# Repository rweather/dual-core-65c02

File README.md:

Dual Core 65C02 Computer
========================

This repository contains schematics, documentation, and program code for my
dual core 65C02 computer.  The computer has two 65C02 microprocessors,
sharing a common memory and I/O bus for symmetric multiprocessing (SMP),
8-bit style.

Here is what it looks like on a PCB.  The two large 40-pin chips at the
top are the CPU's.

If you would like to build your own, I have
[shared the design on PCBway](https://www.pcbway.com/project/shareproject/Dual_Core_65C02_Computer_47504aca.html).  Or contact me at the e-mail address
below and I might still have some spare PCB's I can mail out.

## How did this happen?

Steve Wozniak's design of the Apple II avoided video snow by alternating
access to main memory between the 6502 CPU and the video system.  The two
systems cannot collide and thus cannot create snow.

I asked myself, "Could I do that with two CPU's?" and an obsession was born.

## How does it work?

The W65C02S CPU from Western Digital simplifies things.  The BE
(bus enable) pin can be pulled low to take the CPU completely off the bus
temporarily.  By alternating the bus enables, each CPU can be given
access to memory and I/O in turn.

It would theoretically be possible to do this with the original 6502
microprocessor, but extra bus transceivers would be required as
the original 6502 does not have a BE pin.  The Apple II design
includes bus transceivers for exactly this purpose.

The main 12MHz crystal oscillator is divided down into a number of
component clock signals:

<table border="1">
<tr><td><b>Signal</b></td><td><b>Description</b></td></tr>
<tr><td>CPU1 CLK</td><td>2MHz clock for CPU1</td></tr>
<tr><td>CPU2 CLK</td><td>2MHz clock for CPU2</td></tr>
<tr><td>CPU1 BUSEN</td><td>2MHz bus enable for CPU1</td></tr>
<tr><td>CPU2 BUSEN</td><td>2MHz bus enable for CPU2</td></tr>
<tr><td>COMMON CLK</td><td>4MHz common clock for memory and I/O</td></tr>
</table>

## Memory map

<table border="1">
<tr><td><b>Address Range</b></td><td><b>Description</b></td></tr>
<tr><td>$0000 - $00FF</td><td>Zero page for CPU 1</td></tr>
<tr><td>$0100 - $01FF</td><td>Stack for CPU 1</td></tr>
<tr><td>$0200 - $02FF</td><td>Zero page for CPU 2</td></tr>
<tr><td>$0300 - $03FF</td><td>Stack for CPU 2</td></tr>
<tr><td>$0400 - $7FFF</td><td>Shared RAM (31K)</td></tr>
<tr><td>$8000 - $81FF</td><td>Main board I/O</td></tr>
<tr><td>$8200 - $83FF</td><td>Versatile Interface Adapter (VIA)</td></tr>
<tr><td>$8400 - $84FF</td><td>Asynchronous Communications Interface Adapter (ACIA)</td></tr>
<tr><td>$8600 - $87FF</td><td>RCbus I/O address space</td></tr>
<tr><td>$8800 - $8FFF</td><td>Spare I/O address space</td></tr>
<tr><td>$9000 - $BFFF</td><td>Unused memory space (12K)</td></tr>
<tr><td>$C000 - $FFFF</td><td>CPU-specific ROM (16K)</td></tr>
</table>

Address ranges $0000 - $01FF and $0200 - $03FF are swapped in CPU2 so that
CPU2 sees its zero page and stack starting at $0000 and sees CPU1's
zero page and stack starting at $0200.  This keeps the zero pages and
stacks separate.

The design uses a 32K EEPROM, divided into two 16K halves.  CPU1 sees
the first half of the ROM and CPU2 sees the second half of the ROM.
Thus, different programs can run on each CPU, or the same program.
It is up to the programmer.  This repository contains a minimal
[BIOS](src/common/bios.s) for initializing and accessing the hardware.

The main board decodes 8 I/O device address ranges between $8000 and $8FFF,
each consisting of 512 bytes ($0200 hex).  Four of these are used for
purposes on the main board.  The others are spare for expansion boards.

The 12K of unused memory space can be used for bank-switched RAM, video
memory, cartridge ROM's, or anything you want.

## Mutual exclusion

In any multi-core system, some method is required to synchronise access to
memory and I/O across the cores.  The 65C02 takes multiple clock cycles to
perform a read-modify-write instruction like "INC" or "DEC".  The other core
could get in the middle of that and mess things up.

According to the W65C02S datasheet, the ML pin can be used to co-ordinate
bus accesses when read-modify-write instructions are being performed.
I experimented with a method to "stretch" the bus enable signals to
delay the other CPU while the current one was performing a read-modify-write.
But I wasn't able to make it stable.

Instead, I use two flip-flops and some I/O pins to provide mutual exclusion.
In Logisim, it looks like this:

When CPU1 wants the mutex, it raises the Want1 pin (address $8107, bit 0) and
then polls the Acquired1 signal (address $8080, bit 7).  Once the acquired
signal goes high, CPU1 has the mutex.  To release the mutex, lower the
Want1 pin.

CPU2 does the same thing with Want2 (address $8106, bit 0) and
Acquired2 (address $8080, bit 6).

The mutex is "fair" in the sense that when one CPU lowers its Want pin,
the other CPU is guaranteed to immediately get the mutex if it had
previously raised its Want pin.  It is impossible for one CPU to
hog the mutex, except by forgetting to unlock it.

The [BIOS](src/common/bios.s) provides the subroutines `mutex_lock`,
`mutex_unlock`, and `mutex_try_lock` to make things easier for the
programmer.  The implementation is different for each CPU.

## System millisecond tick timer

There is a 555 timer in the circuit that delivers a 1000Hz signal to the
NMI pins on each of the CPU's.  A potentiometer allows the frequency to
be dialed in precisely.

The default NMI handler in the BIOS increments a 24-bit millisecond
tick counter which wraps around after 4 hours and 39 minutes.
Call the `systick` subroutine to fetch the value of the tick counter
safely into the Y:X:A register triple.

NMI can interfere with foreground code and regular IRQ handlers,
which may affect timing-critical code.  There are jumpers in the circuit
that allow the 555 to be disconnected from one or both of the CPU's.

## Schematic and other technical information

* [PDF of the schematic](schematics/DualCore6502Whole/PDF/DualCore6502Whole.pdf)
* [Gerbers for the PCB](schematics/DualCore6502Whole/Gerber)
* [Parts list](doc/parts-list.md)

## What can't it do?

DMA is not currently supported.  Pausing the clocks and bus enables to allow
external access to the bus is complicated.  Too complicated for my feeble brain.
Maybe in the next version.

In theory the W65C02S can go up to 14MHz.  While SRAM that is faster than
70ns access time is possible, AT28C256 EEPROM chips form are typically 150ns.
In practice, this limits the maximum memory speed to about 4MHz.
AT27C256 EEPROM's can go down to 45ns but they are not pin-compatible and
that still only gets us to 8MHz or so.  An alternative memory design with
wait states may allow pushing the performance further.  Once again,
my feeble brain isn't up to the task.

Could we have more CPU's?  Four?  Eight?  In theory, yes.  But memory
access times limit things.  The speed of the individual CPU's would need to be
reduced to 1MHz to allow four on the bus, executing one after another.
The effective speed of the system would remain at 4MHz.  An alternate design
might give each CPU its own fast SRAM, with wait states for access to
common RAM, ROM, and I/O.

## TODO

* Machine monitor for loading programs into RAM via the serial port and
debugging them (partially done).
* Devise a multi-core operating system to showcase the capabilities.

## License

Distributed under the terms of the MIT license.

## Contact

For more information on this code, to report bugs, or to suggest
improvements, please contact the author Rhys Weatherley via
[email](mailto:rhys.weatherley@gmail.com).

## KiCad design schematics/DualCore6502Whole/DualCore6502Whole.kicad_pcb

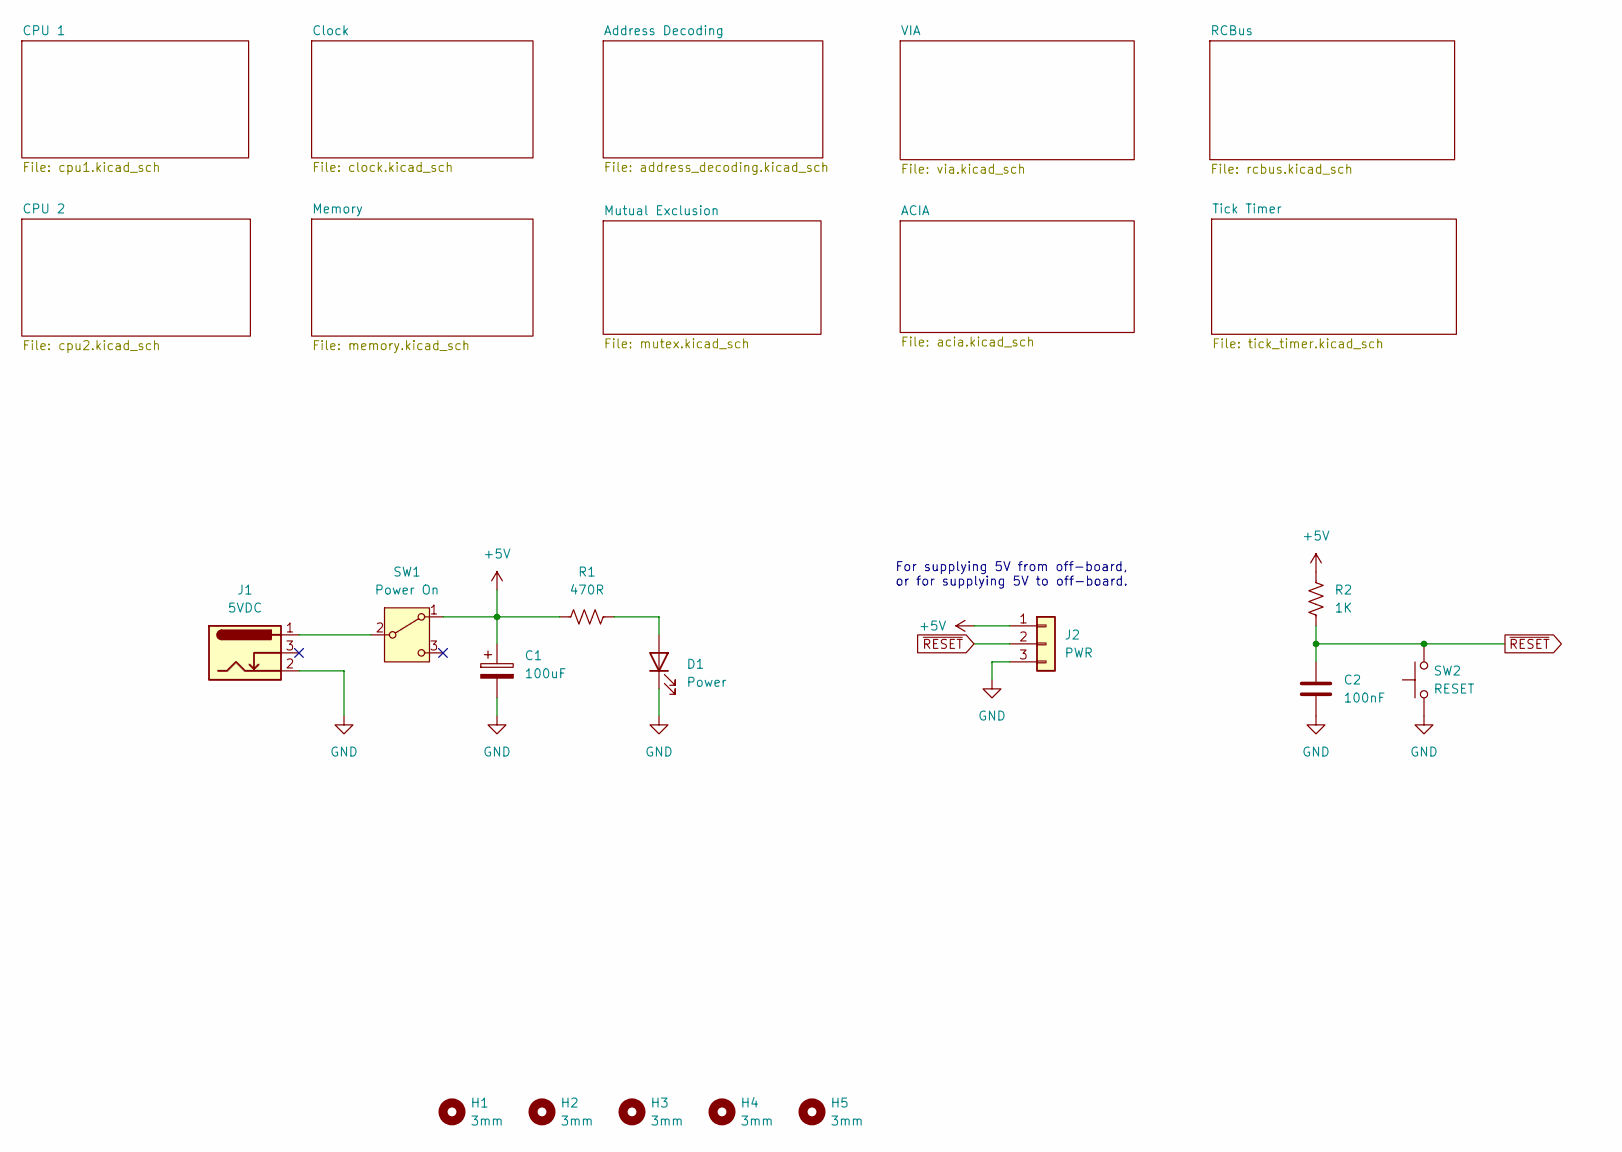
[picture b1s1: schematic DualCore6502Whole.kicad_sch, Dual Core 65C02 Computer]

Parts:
C1: 100uF; CP_Radial_D6.3mm_P2.50mm
C2: 100nF; C_Disc_D5.0mm_W2.5mm_P5.00mm
D1: Power; LED_D5.0mm
H1, H2, H3, H4, H5: 3mm; MountingHole_3mm
J1: 5VDC; BarrelJack_Horizontal
J2: PWR; PhoenixContact_MC_1,5_3-G-5.08_1x03_P5.08mm_Horizontal
R1: 470R; R_Axial_DIN0207_L6.3mm_D2.5mm_P10.16mm_Horizontal
R2: 1K; R_Axial_DIN0207_L6.3mm_D2.5mm_P10.16mm_Horizontal
SW1: Power On; PinHeader_1x03_P2.54mm_Vertical
SW2: RESET; SW_PUSH_6mm_H5mm

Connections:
+5V: C1.1, J2.1, R1.1, R2.1, SW1.1 (A); also elsewhere on the board
GND: C1.2, C2.2, D1.1 (K), J1.2, J2.3, SW2.1; also elsewhere on the board
unnamed: D1.2 (A), R1.2
unnamed: J1.1, SW1.2 (B)
~RESET: C2.1, J2.2, R2.2, SW2.2; also elsewhere on the board

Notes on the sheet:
For supplying 5V from off-board, or for supplying 5V to off-board.

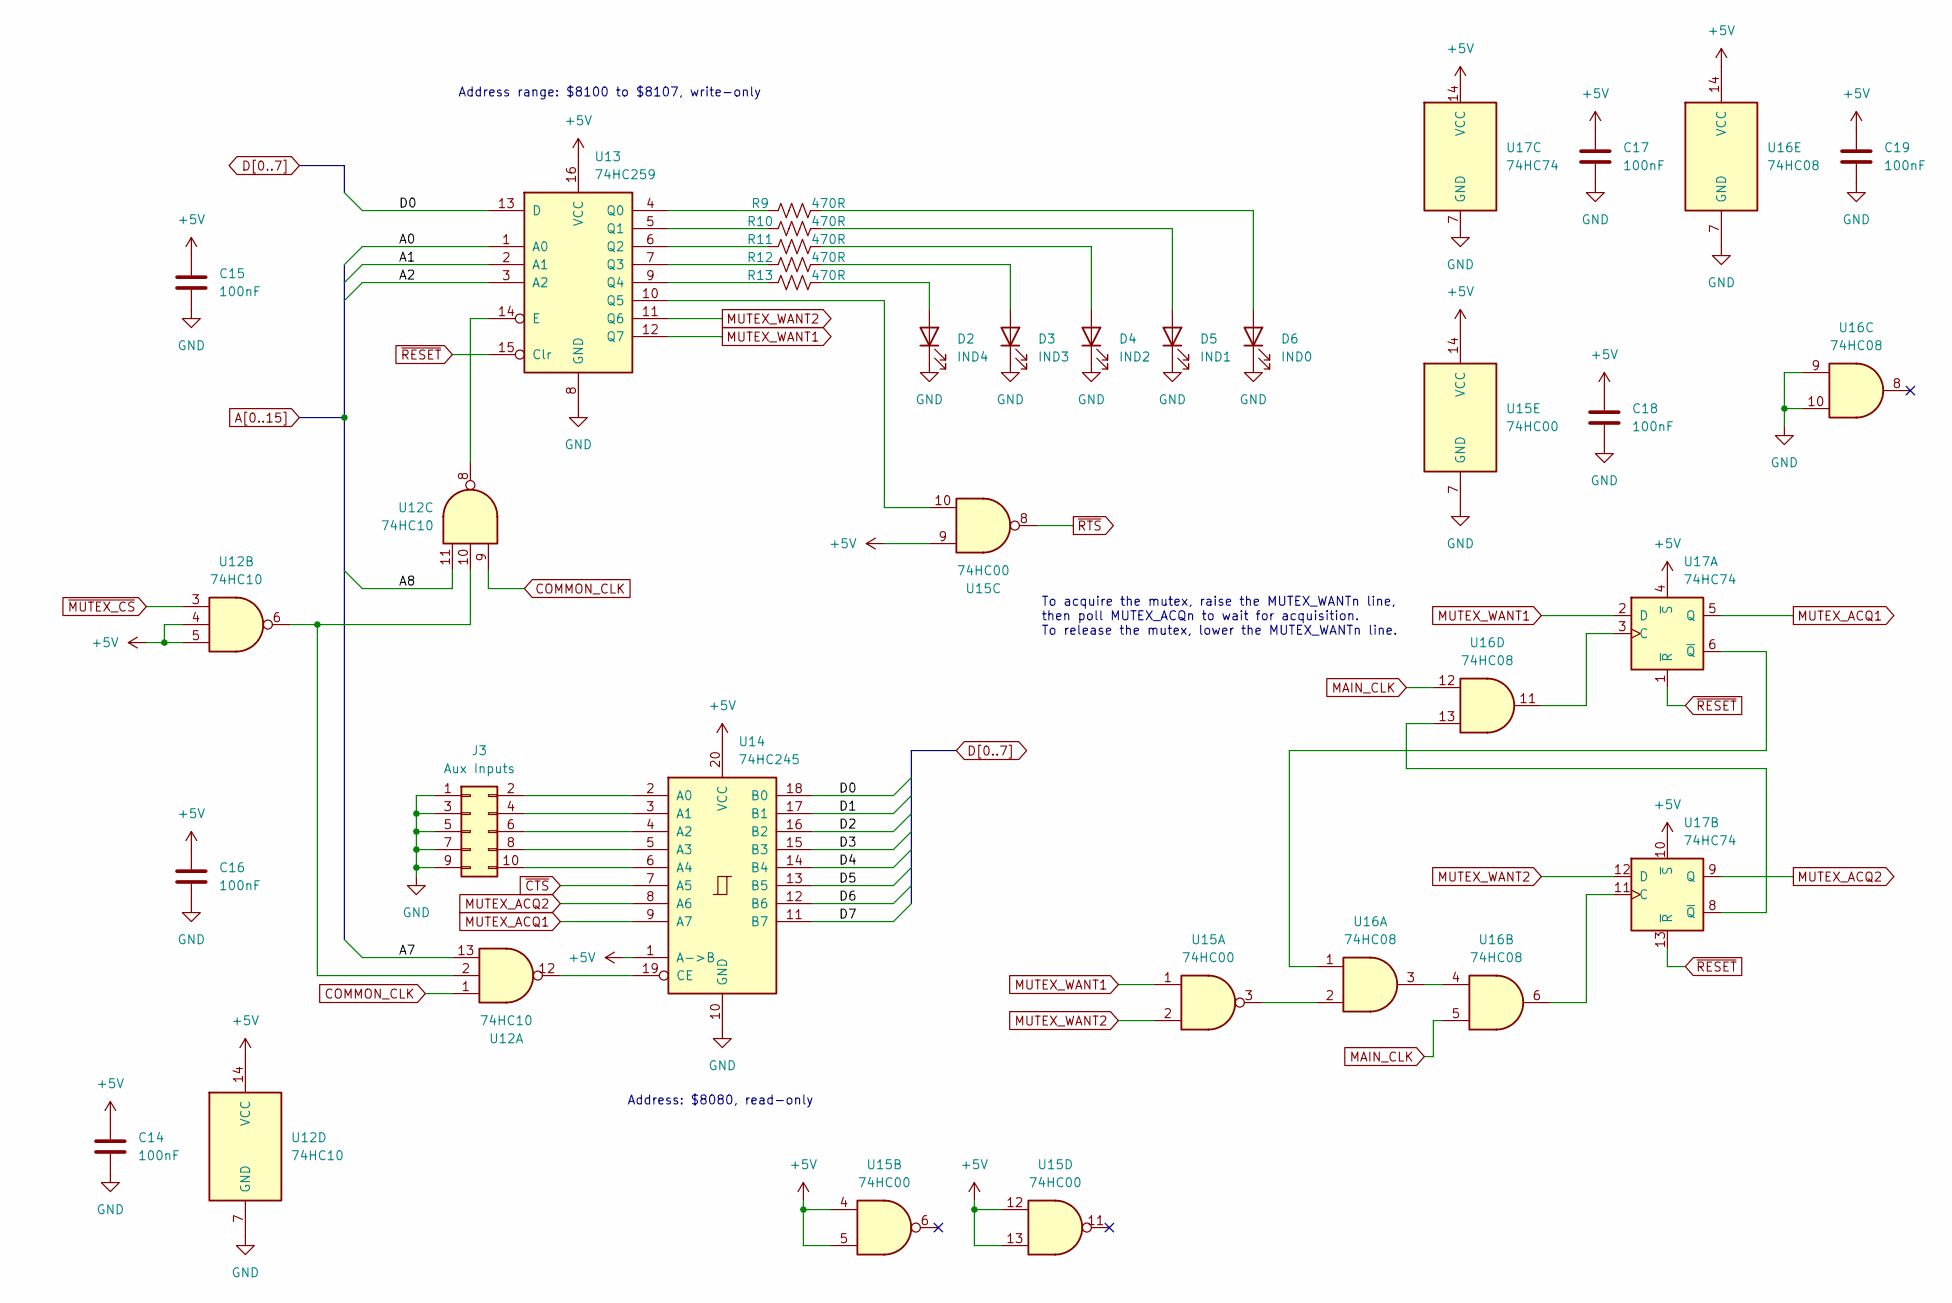
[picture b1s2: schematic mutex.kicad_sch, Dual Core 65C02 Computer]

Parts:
C14, C15, C16, C17, C18, C19: 100nF; C_Disc_D5.0mm_W2.5mm_P5.00mm
D2: IND4; LED_D3.0mm
D3: IND3; LED_D3.0mm
D4: IND2; LED_D3.0mm
D5: IND1; LED_D3.0mm
D6: IND0; LED_D3.0mm
J3: Aux Inputs; PinHeader_2x05_P2.54mm_Vertical
R9, R10, R11, R12, R13: 470R; R_Axial_DIN0207_L6.3mm_D2.5mm_P10.16mm_Horizontal
U12: 74HC10; DIP-14_W7.62mm_Socket
U13: 74HC259; DIP-16_W7.62mm_Socket
U14: 74HC245; DIP-20_W7.62mm_Socket
U15: 74HC00; DIP-14_W7.62mm_Socket
U16: 74HC08; DIP-14_W7.62mm_Socket
U17: 74HC74; DIP-14_W7.62mm_Socket

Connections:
+5V: C14.1, C15.1, C16.1, C17.1, C18.1, C19.1, U12.4, U12.5, U12.14 (VCC), U13.16 (VCC), U14.1 (A->B), U14.20 (VCC), U15.4, U15.5, U15.9, U15.12, U15.13, U15.14 (VCC), U16.14 (VCC), U17.4 (~S), U17.10 (~S), U17.14 (VCC); also elsewhere on the board
A0: U13.1 (A0); also elsewhere on the board
A1: U13.2 (A1); also elsewhere on the board
A2: U13.3 (A2); also elsewhere on the board
A7: U12.13; also elsewhere on the board
A8: U12.11; also elsewhere on the board
COMMON_CLK: U12.1, U12.9; also elsewhere on the board
D0: U13.13 (D), U14.18 (B0); also elsewhere on the board
D1: U14.17 (B1); also elsewhere on the board
D2: U14.16 (B2); also elsewhere on the board
D3: U14.15 (B3); also elsewhere on the board
D4: U14.14 (B4); also elsewhere on the board
D5: U14.13 (B5); also elsewhere on the board
D6: U14.12 (B6); also elsewhere on the board
D7: U14.11 (B7); also elsewhere on the board
GND: C14.2, C15.2, C16.2, C17.2, C18.2, C19.2, D2.1 (K), D3.1 (K), D4.1 (K), D5.1 (K), D6.1 (K), J3.1, J3.3, J3.5, J3.7, J3.9, U12.7 (GND), U13.8 (GND), U14.10 (GND), U15.7 (GND), U16.7 (GND), U16.9, U16.10, U17.7 (GND); also elsewhere on the board
MAIN_CLK: U16.5, U16.12; also elsewhere on the board
MUTEX_ACQ1: U14.9 (A7), U17.5 (Q)
MUTEX_ACQ2: U14.8 (A6), U17.9 (Q)
MUTEX_WANT1: U13.12 (Q7), U15.1, U17.2 (D)
MUTEX_WANT2: U13.11 (Q6), U15.2, U17.12 (D)
unnamed: D2.2 (A), R13.2
unnamed: D3.2 (A), R12.2
unnamed: D4.2 (A), R11.2
unnamed: D5.2 (A), R10.2
unnamed: D6.2 (A), R9.2
unnamed: J3.2, U14.2 (A0)
unnamed: J3.4, U14.3 (A1)
unnamed: J3.6, U14.4 (A2)
unnamed: J3.8, U14.5 (A3)
unnamed: J3.10, U14.6 (A4)
unnamed: U12.2, U12.6, U12.10
unnamed: U12.8, U13.14 (E)
unnamed: R9.1, U13.4 (Q0)
unnamed: R10.1, U13.5 (Q1)
unnamed: R11.1, U13.6 (Q2)
unnamed: R12.1, U13.7 (Q3)
unnamed: R13.1, U13.9 (Q4)
unnamed: U13.10 (Q5), U15.10
unnamed: U12.12, U14.19 (CE)
unnamed: U15.3, U16.2
unnamed: U16.3, U16.4
unnamed: U16.11, U17.3 (C)
unnamed: U16.1, U17.6 (~Q)
unnamed: U16.6, U17.11 (C)
unnamed: U16.13, U17.8 (~Q)
~CTS: U14.7 (A5); also elsewhere on the board
~MUTEX_CS: U12.3; also elsewhere on the board
~RESET: U13.15 (Clr), U17.1 (~R), U17.13 (~R); also elsewhere on the board
~RTS: U15.8; also elsewhere on the board

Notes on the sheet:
Address range: $8100 to $8107, write-only
Address: $8080, read-only
To acquire the mutex, raise the MUTEX_WANTn line, then poll MUTEX_ACQn to wait for acquisition. To release the mutex, lower the MUTEX_WANTn line.

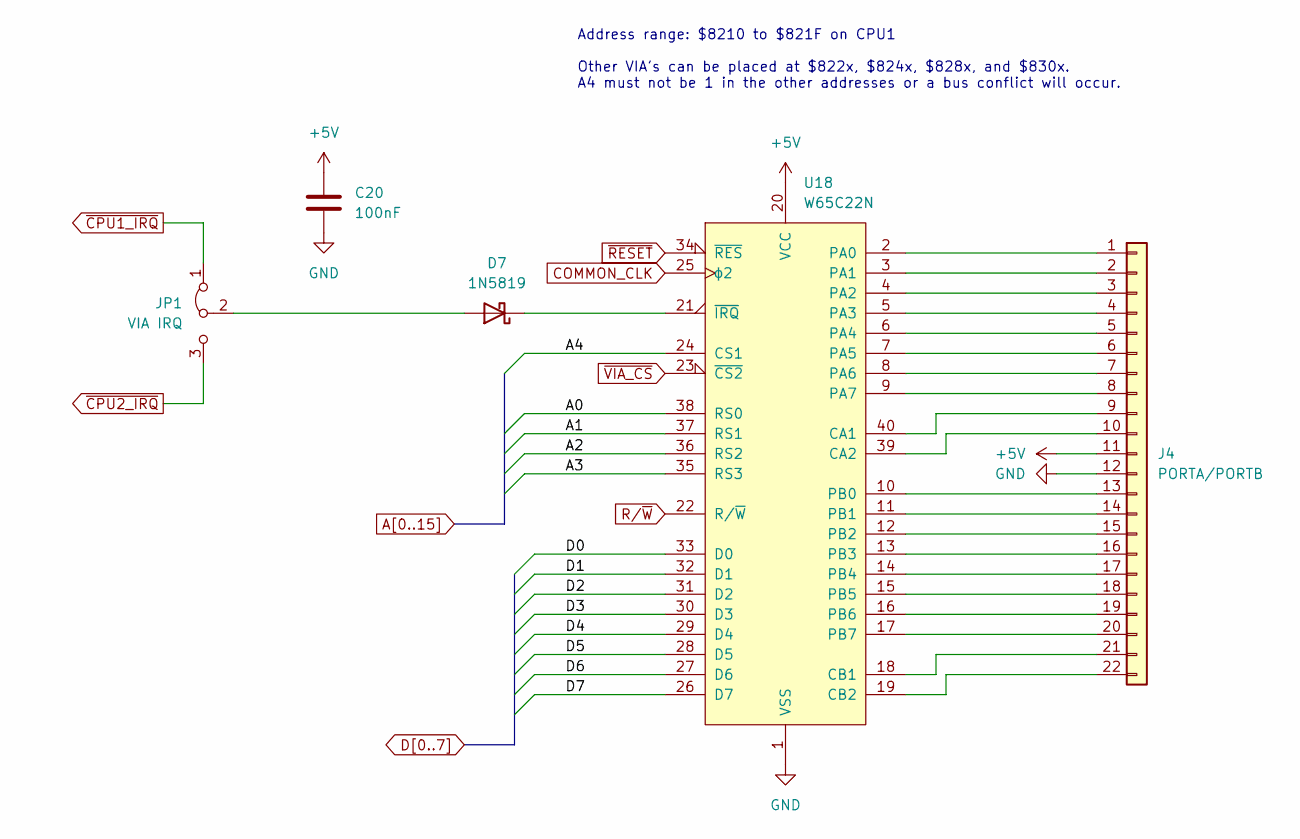
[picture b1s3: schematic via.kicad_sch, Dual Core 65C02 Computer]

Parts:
C20: 100nF; C_Disc_D5.0mm_W2.5mm_P5.00mm
D7: 1N5819; D_DO-41_SOD81_P10.16mm_Horizontal
J4: PORTA/PORTB; PinSocket_1x22_P2.54mm_Vertical
JP1: VIA IRQ; PinHeader_1x03_P2.54mm_Vertical
U18: W65C22N; DIP-40_W15.24mm_Socket

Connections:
+5V: C20.1, J4.11, U18.20 (VCC); also elsewhere on the board
A0: U18.38 (RS0); also elsewhere on the board
A1: U18.37 (RS1); also elsewhere on the board
A2: U18.36 (RS2); also elsewhere on the board
A3: U18.35 (RS3); also elsewhere on the board
A4: U18.24 (CS1); also elsewhere on the board
COMMON_CLK: U18.25 (ϕ2); also elsewhere on the board
D0: U18.33 (D0); also elsewhere on the board
D1: U18.32 (D1); also elsewhere on the board
D2: U18.31 (D2); also elsewhere on the board
D3: U18.30 (D3); also elsewhere on the board
D4: U18.29 (D4); also elsewhere on the board
D5: U18.28 (D5); also elsewhere on the board
D6: U18.27 (D6); also elsewhere on the board
D7: U18.26 (D7); also elsewhere on the board
GND: C20.2, J4.12, U18.1 (VSS); also elsewhere on the board
unnamed: D7.2 (A), JP1.2 (C)
unnamed: D7.1 (K), U18.21 (~IRQ)
unnamed: J4.1, U18.2 (PA0)
unnamed: J4.2, U18.3 (PA1)
unnamed: J4.3, U18.4 (PA2)
unnamed: J4.4, U18.5 (PA3)
unnamed: J4.5, U18.6 (PA4)
unnamed: J4.6, U18.7 (PA5)
unnamed: J4.7, U18.8 (PA6)
unnamed: J4.8, U18.9 (PA7)
unnamed: J4.9, U18.40 (CA1)
unnamed: J4.10, U18.39 (CA2)
unnamed: J4.13, U18.10 (PB0)
unnamed: J4.14, U18.11 (PB1)
unnamed: J4.15, U18.12 (PB2)
unnamed: J4.16, U18.13 (PB3)
unnamed: J4.17, U18.14 (PB4)
unnamed: J4.18, U18.15 (PB5)
unnamed: J4.19, U18.16 (PB6)
unnamed: J4.20, U18.17 (PB7)
unnamed: J4.21, U18.18 (CB1)
unnamed: J4.22, U18.19 (CB2)
R/~W: U18.22 (R/~W); also elsewhere on the board
~CPU1_IRQ: JP1.1 (A); also elsewhere on the board
~CPU2_IRQ: JP1.3 (B); also elsewhere on the board
~RESET: U18.34 (~RES); also elsewhere on the board
~VIA_CS: U18.23 (~CS2); also elsewhere on the board

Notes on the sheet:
Address range: $8210 to $821F on CPU1 Other VIA's can be placed at $822x, $824x, $828x, and $830x. A4 must not be 1 in the other addresses or a bus conflict will occur.

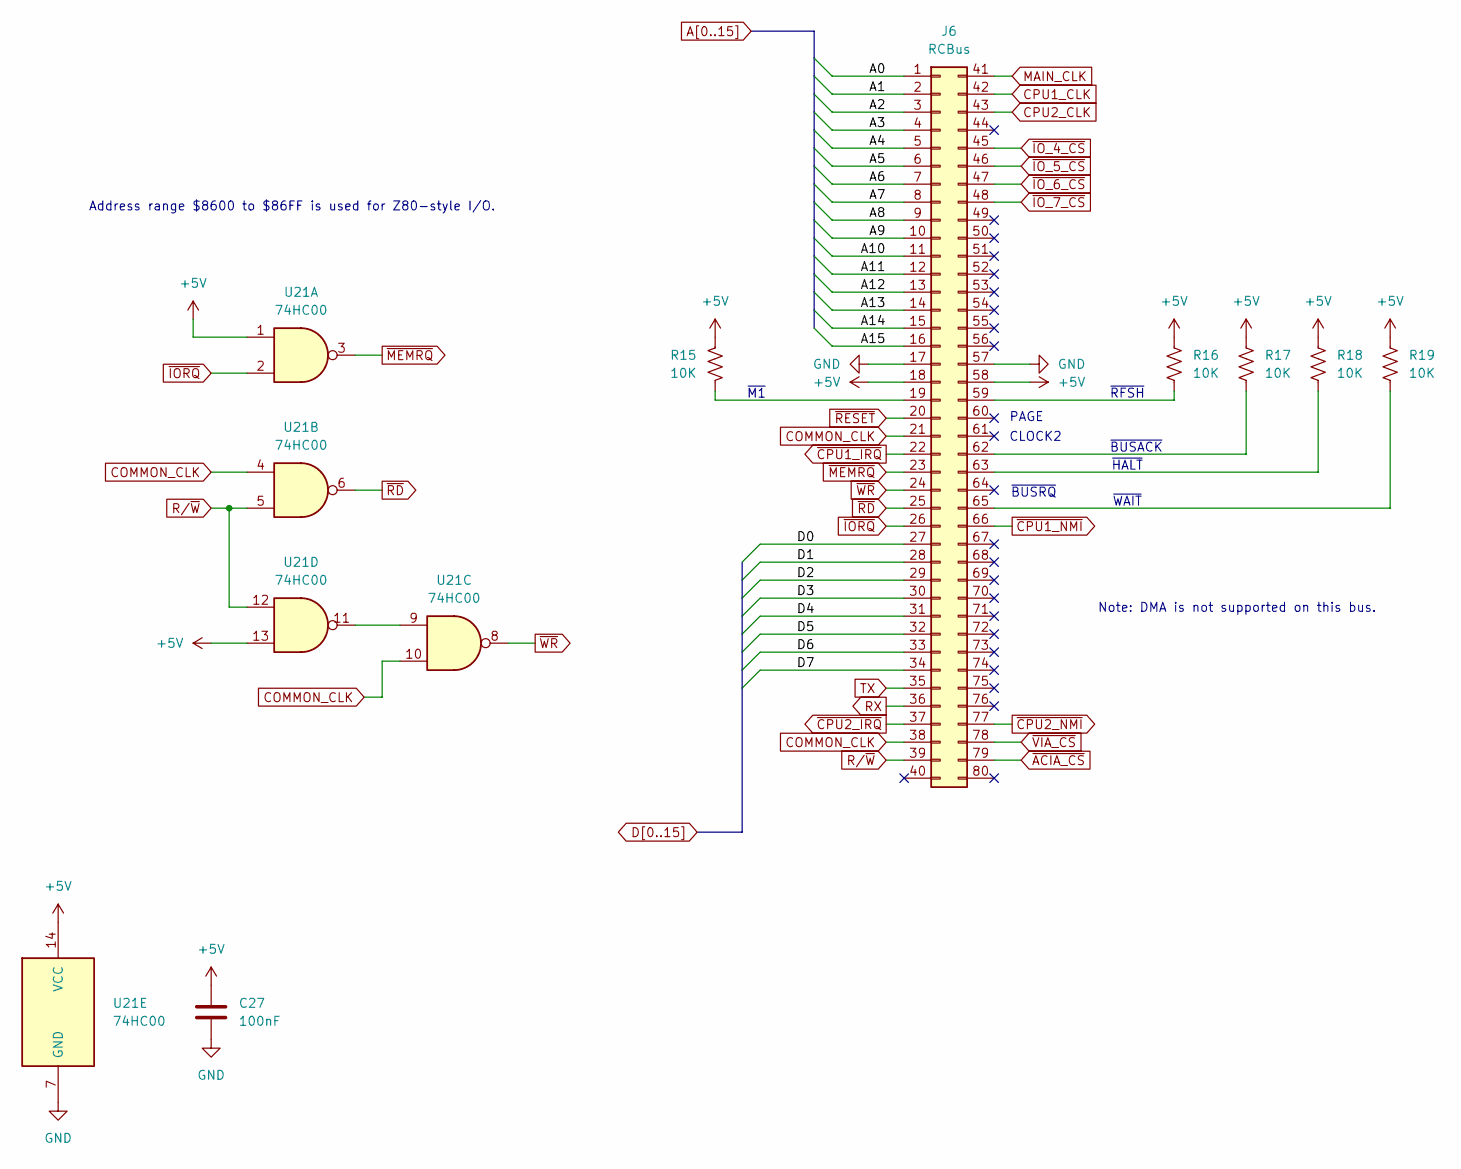
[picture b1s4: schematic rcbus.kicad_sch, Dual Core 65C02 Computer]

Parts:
C27: 100nF; C_Disc_D5.0mm_W2.5mm_P5.00mm
J6: RCBus; RCBus_PinSocket_2x40_P2.54mm_Vertical_DC
R15, R16, R17, R18, R19: 10K; R_Axial_DIN0207_L6.3mm_D2.5mm_P10.16mm_Horizontal
U21: 74HC00; DIP-14_W7.62mm_Socket

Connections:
+5V: C27.1, J6.18, J6.58, R15.1, R16.1, R17.1, R18.1, R19.1, U21.1, U21.13, U21.14 (VCC); also elsewhere on the board
A0: J6.1; also elsewhere on the board
A1: J6.2; also elsewhere on the board
A2: J6.3; also elsewhere on the board
A3: J6.4; also elsewhere on the board
A4: J6.5; also elsewhere on the board
A5: J6.6; also elsewhere on the board
A6: J6.7; also elsewhere on the board
A7: J6.8; also elsewhere on the board
A8: J6.9; also elsewhere on the board
A9: J6.10; also elsewhere on the board
A10: J6.11; also elsewhere on the board
A11: J6.12; also elsewhere on the board
A12: J6.13; also elsewhere on the board
A13: J6.14; also elsewhere on the board
A14: J6.15; also elsewhere on the board
A15: J6.16; also elsewhere on the board
COMMON_CLK: J6.21, J6.38, U21.4, U21.10; also elsewhere on the board
CPU1_CLK: J6.42; also elsewhere on the board
CPU2_CLK: J6.43; also elsewhere on the board
D0: J6.27; also elsewhere on the board
D1: J6.28; also elsewhere on the board
D2: J6.29; also elsewhere on the board
D3: J6.30; also elsewhere on the board
D4: J6.31; also elsewhere on the board
D5: J6.32; also elsewhere on the board
D6: J6.33; also elsewhere on the board
D7: J6.34; also elsewhere on the board
GND: C27.2, J6.17, J6.57, U21.7 (GND); also elsewhere on the board
MAIN_CLK: J6.41; also elsewhere on the board
unnamed: J6.19, R15.2
unnamed: J6.59, R16.2
unnamed: J6.62, R17.2
unnamed: J6.63, R18.2
unnamed: J6.65, R19.2
unnamed: U21.9, U21.11
RX: J6.36; also elsewhere on the board
R/~W: J6.39, U21.5, U21.12; also elsewhere on the board
TX: J6.35; also elsewhere on the board
~ACIA_CS: J6.79; also elsewhere on the board
~CPU1_IRQ: J6.22; also elsewhere on the board
~CPU1_NMI: J6.66; also elsewhere on the board
~CPU2_IRQ: J6.37; also elsewhere on the board
~CPU2_NMI: J6.77; also elsewhere on the board
~IORQ: J6.26, U21.2; also elsewhere on the board
~IO_4_CS: J6.45; also elsewhere on the board
~IO_5_CS: J6.46; also elsewhere on the board
~IO_6_CS: J6.47; also elsewhere on the board
~IO_7_CS: J6.48; also elsewhere on the board
~MEMRQ: J6.23, U21.3
~RD: J6.25, U21.6
~RESET: J6.20; also elsewhere on the board
~VIA_CS: J6.78; also elsewhere on the board
~WR: J6.24, U21.8

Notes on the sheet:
~{RFSH}
~{M1}
~{WAIT}
PAGE
~{BUSRQ}
~{HALT}
CLOCK2
Address range $8600 to $86FF is used for Z80-style I/O.
~{BUSACK}
Note: DMA is not supported on this bus.

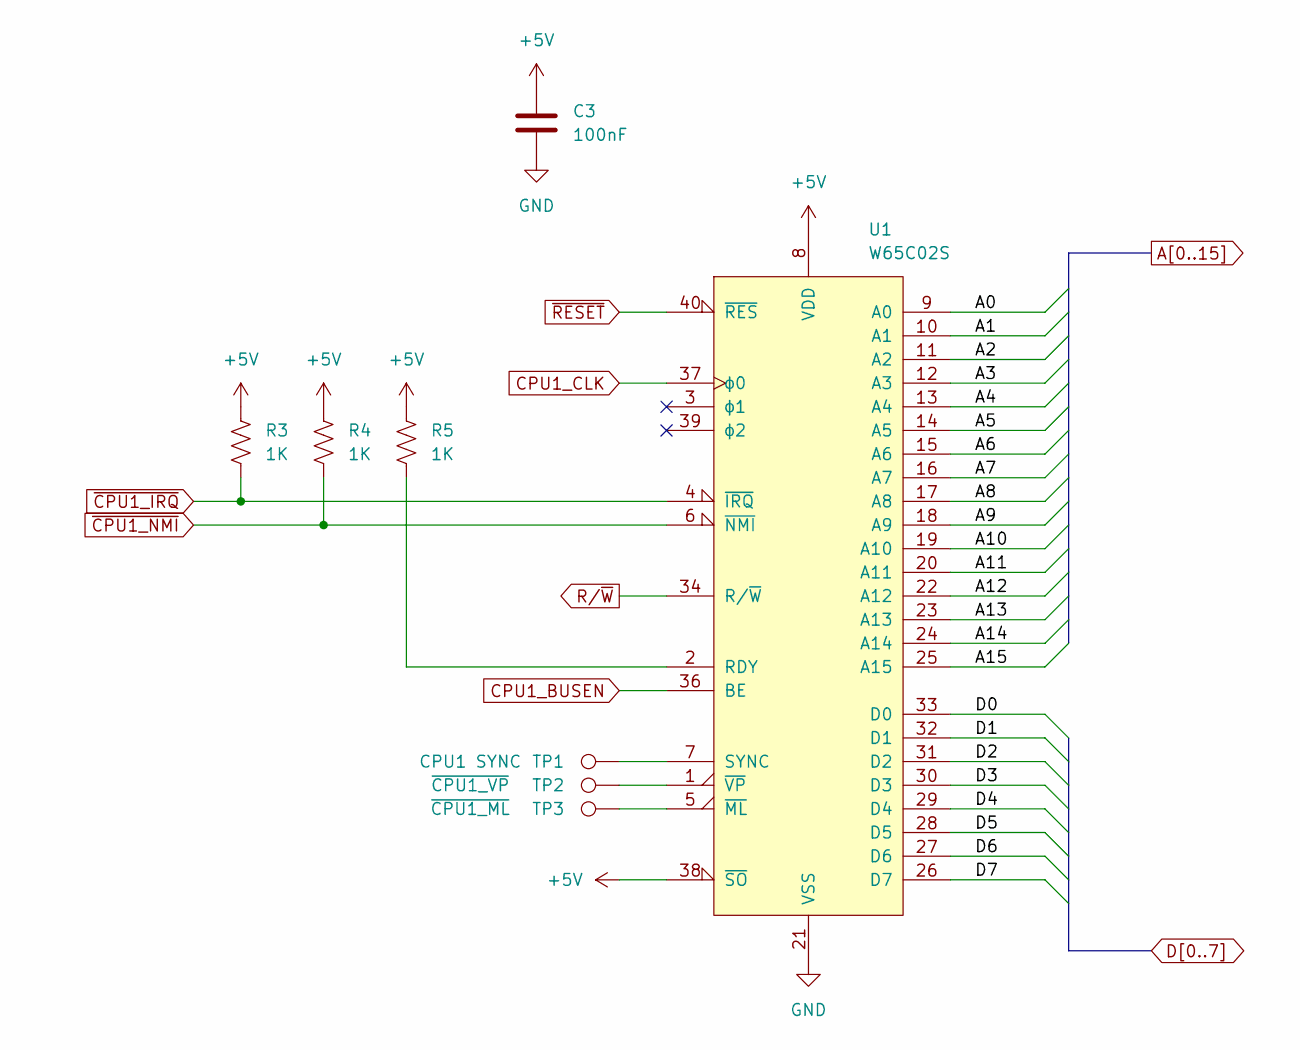
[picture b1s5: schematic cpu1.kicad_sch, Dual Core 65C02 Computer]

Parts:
C3: 100nF; C_Disc_D5.0mm_W2.5mm_P5.00mm
R3, R4, R5: 1K; R_Axial_DIN0207_L6.3mm_D2.5mm_P10.16mm_Horizontal
TP1: CPU1 SYNC; TestPoint_Pad_D1.5mm
TP2: ~{CPU1_VP}; TestPoint_Pad_D1.5mm
TP3: ~{CPU1_ML}; TestPoint_Pad_D1.5mm
U1: W65C02S; DIP-40_W15.24mm_Socket

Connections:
+5V: C3.1, R3.1, R4.1, R5.1, U1.8 (VDD), U1.38 (~SO); also elsewhere on the board
A0: U1.9 (A0); also elsewhere on the board
A1: U1.10 (A1); also elsewhere on the board
A2: U1.11 (A2); also elsewhere on the board
A3: U1.12 (A3); also elsewhere on the board
A4: U1.13 (A4); also elsewhere on the board
A5: U1.14 (A5); also elsewhere on the board
A6: U1.15 (A6); also elsewhere on the board
A7: U1.16 (A7); also elsewhere on the board
A8: U1.17 (A8); also elsewhere on the board
A9: U1.18 (A9); also elsewhere on the board
A10: U1.19 (A10); also elsewhere on the board
A11: U1.20 (A11); also elsewhere on the board
A12: U1.22 (A12); also elsewhere on the board
A13: U1.23 (A13); also elsewhere on the board
A14: U1.24 (A14); also elsewhere on the board
A15: U1.25 (A15); also elsewhere on the board
CPU1_BUSEN: U1.36 (BE); also elsewhere on the board
CPU1_CLK: U1.37 (ϕ0); also elsewhere on the board
D0: U1.33 (D0); also elsewhere on the board
D1: U1.32 (D1); also elsewhere on the board
D2: U1.31 (D2); also elsewhere on the board
D3: U1.30 (D3); also elsewhere on the board
D4: U1.29 (D4); also elsewhere on the board
D5: U1.28 (D5); also elsewhere on the board
D6: U1.27 (D6); also elsewhere on the board
D7: U1.26 (D7); also elsewhere on the board
GND: C3.2, U1.21 (VSS); also elsewhere on the board
unnamed: R5.2, U1.2 (RDY)
unnamed: TP1.1, U1.7 (SYNC)
unnamed: TP3.1, U1.5 (~ML)
unnamed: TP2.1, U1.1 (~VP)
R/~W: U1.34 (R/~W); also elsewhere on the board
~CPU1_IRQ: R3.2, U1.4 (~IRQ); also elsewhere on the board
~CPU1_NMI: R4.2, U1.6 (~NMI); also elsewhere on the board
~RESET: U1.40 (~RES); also elsewhere on the board

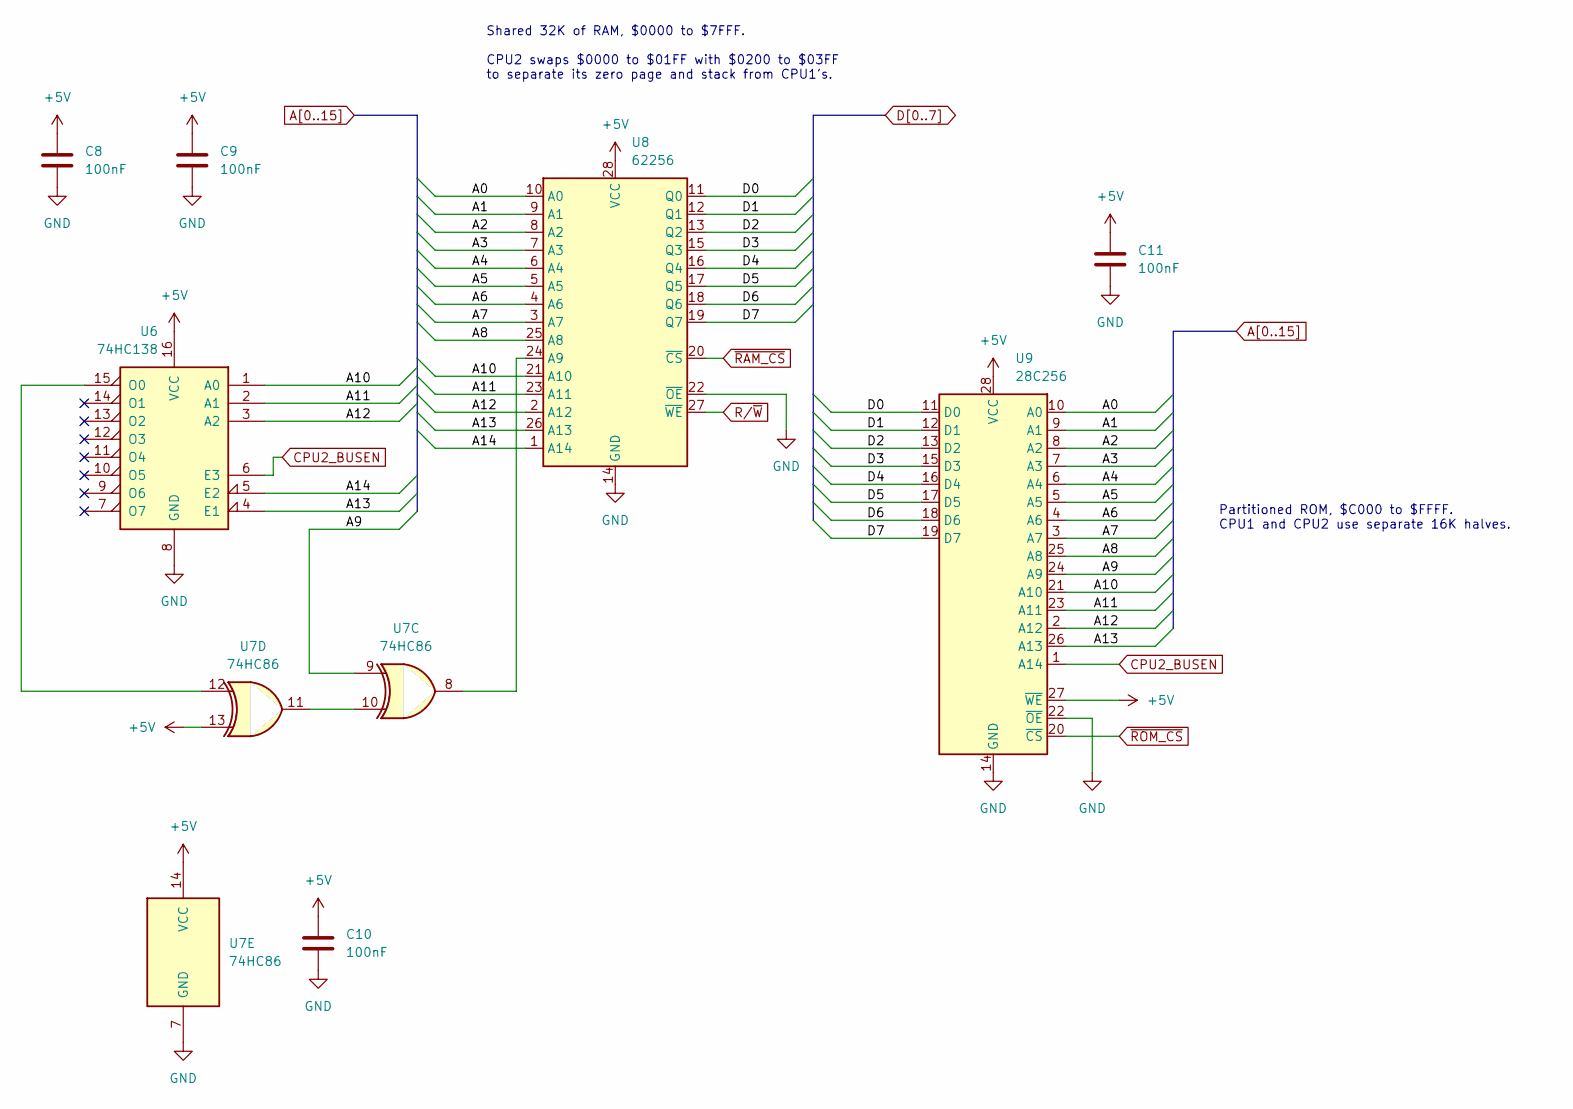
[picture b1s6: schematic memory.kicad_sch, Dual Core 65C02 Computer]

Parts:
C8, C9, C10, C11: 100nF; C_Disc_D5.0mm_W2.5mm_P5.00mm
U6: 74HC138; DIP-16_W7.62mm_Socket
U7: 74HC86; DIP-14_W7.62mm_Socket
U8: 62256; DIP-28_W15.24mm_Socket
U9: 28C256; DIP_Socket-28_W11.9_W12.7_W15.24_W17.78_W18.5_3M_228-1277-0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

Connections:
+5V: C8.1, C9.1, C10.1, C11.1, U6.16 (VCC), U7.13, U7.14 (VCC), U8.28 (VCC), U9.27 (~WE), U9.28 (VCC); also elsewhere on the board
A0: U8.10 (A0), U9.10 (A0); also elsewhere on the board
A1: U8.9 (A1), U9.9 (A1); also elsewhere on the board
A2: U8.8 (A2), U9.8 (A2); also elsewhere on the board
A3: U8.7 (A3), U9.7 (A3); also elsewhere on the board
A4: U8.6 (A4), U9.6 (A4); also elsewhere on the board
A5: U8.5 (A5), U9.5 (A5); also elsewhere on the board
A6: U8.4 (A6), U9.4 (A6); also elsewhere on the board
A7: U8.3 (A7), U9.3 (A7); also elsewhere on the board
A8: U8.25 (A8), U9.25 (A8); also elsewhere on the board
A9: U7.9, U9.24 (A9); also elsewhere on the board
A10: U6.1 (A0), U8.21 (A10), U9.21 (A10); also elsewhere on the board
A11: U6.2 (A1), U8.23 (A11), U9.23 (A11); also elsewhere on the board
A12: U6.3 (A2), U8.2 (A12), U9.2 (A12); also elsewhere on the board
A13: U6.4 (E1), U8.26 (A13), U9.26 (A13); also elsewhere on the board
A14: U6.5 (E2), U8.1 (A14); also elsewhere on the board
CPU2_BUSEN: U6.6 (E3), U9.1 (A14); also elsewhere on the board
D0: U8.11 (Q0), U9.11 (D0); also elsewhere on the board
D1: U8.12 (Q1), U9.12 (D1); also elsewhere on the board
D2: U8.13 (Q2), U9.13 (D2); also elsewhere on the board
D3: U8.15 (Q3), U9.15 (D3); also elsewhere on the board
D4: U8.16 (Q4), U9.16 (D4); also elsewhere on the board
D5: U8.17 (Q5), U9.17 (D5); also elsewhere on the board
D6: U8.18 (Q6), U9.18 (D6); also elsewhere on the board
D7: U8.19 (Q7), U9.19 (D7); also elsewhere on the board
GND: C8.2, C9.2, C10.2, C11.2, U6.8 (GND), U7.7 (GND), U8.14 (GND), U8.22 (~OE), U9.14 (GND), U9.22 (~OE); also elsewhere on the board
unnamed: U6.15 (O0), U7.12
unnamed: U7.10, U7.11
unnamed: U7.8, U8.24 (A9)
R/~W: U8.27 (~WE); also elsewhere on the board
~RAM_CS: U8.20 (~CS); also elsewhere on the board
~ROM_CS: U9.20 (~CS); also elsewhere on the board

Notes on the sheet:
Shared 32K of RAM, $0000 to $7FFF. CPU2 swaps $0000 to $01FF with $0200 to $03FF to separate its zero page and stack from CPU1's.
Partitioned ROM, $C000 to $FFFF. CPU1 and CPU2 use separate 16K halves.

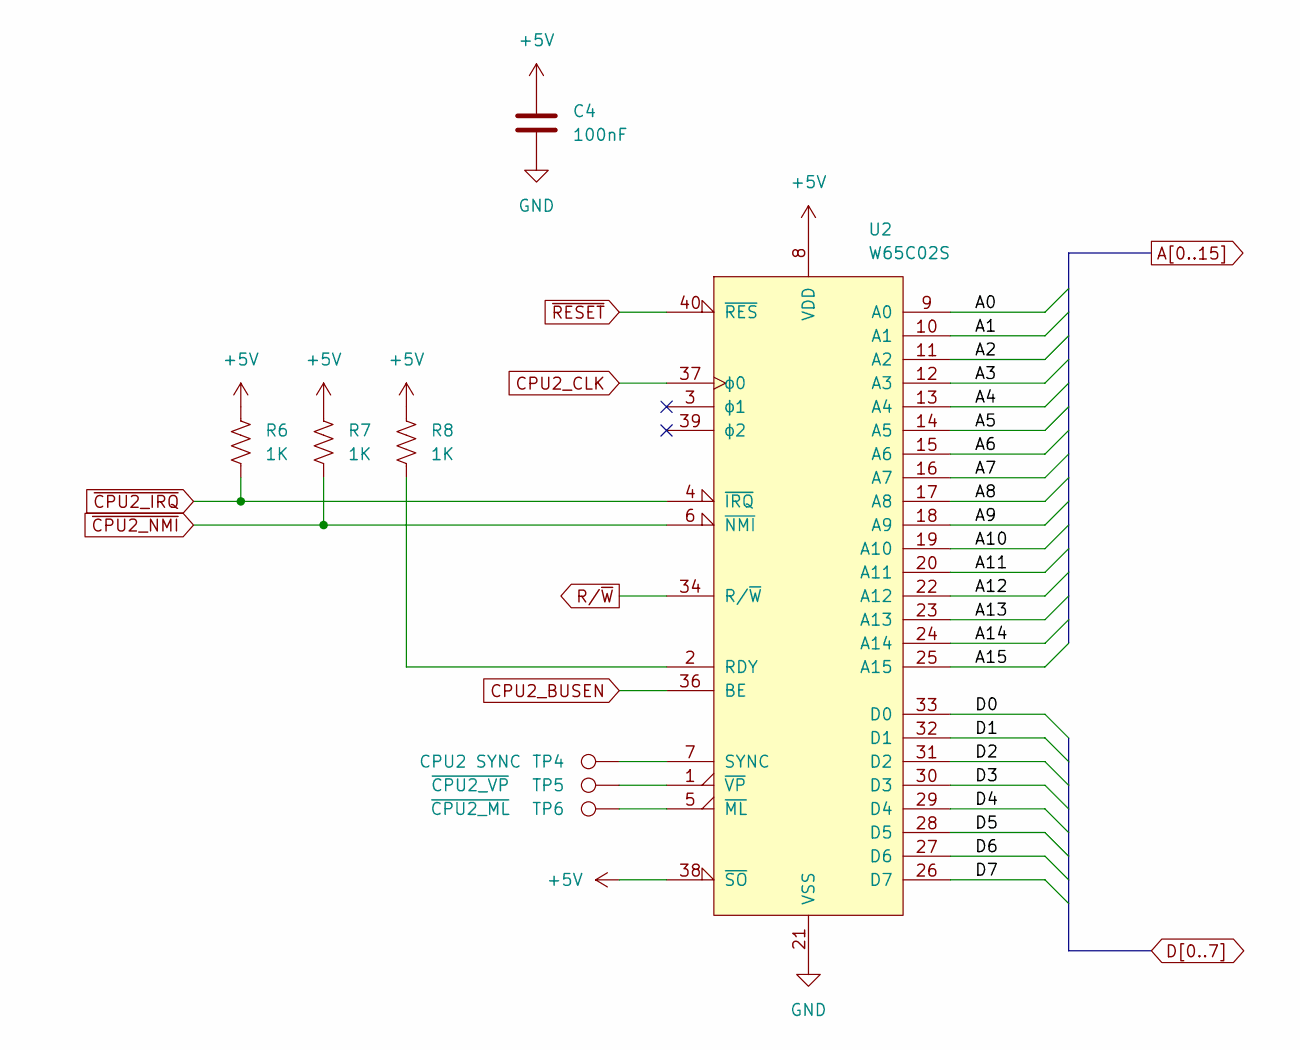
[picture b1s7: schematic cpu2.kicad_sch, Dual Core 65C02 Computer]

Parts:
C4: 100nF; C_Disc_D5.0mm_W2.5mm_P5.00mm
R6, R7, R8: 1K; R_Axial_DIN0207_L6.3mm_D2.5mm_P10.16mm_Horizontal
TP4: CPU2 SYNC; TestPoint_Pad_D1.5mm
TP5: ~{CPU2_VP}; TestPoint_Pad_D1.5mm
TP6: ~{CPU2_ML}; TestPoint_Pad_D1.5mm
U2: W65C02S; DIP-40_W15.24mm_Socket

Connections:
+5V: C4.1, R6.1, R7.1, R8.1, U2.8 (VDD), U2.38 (~SO); also elsewhere on the board
A0: U2.9 (A0); also elsewhere on the board
A1: U2.10 (A1); also elsewhere on the board
A2: U2.11 (A2); also elsewhere on the board
A3: U2.12 (A3); also elsewhere on the board
A4: U2.13 (A4); also elsewhere on the board
A5: U2.14 (A5); also elsewhere on the board
A6: U2.15 (A6); also elsewhere on the board
A7: U2.16 (A7); also elsewhere on the board
A8: U2.17 (A8); also elsewhere on the board
A9: U2.18 (A9); also elsewhere on the board
A10: U2.19 (A10); also elsewhere on the board
A11: U2.20 (A11); also elsewhere on the board
A12: U2.22 (A12); also elsewhere on the board
A13: U2.23 (A13); also elsewhere on the board
A14: U2.24 (A14); also elsewhere on the board
A15: U2.25 (A15); also elsewhere on the board
CPU2_BUSEN: U2.36 (BE); also elsewhere on the board
CPU2_CLK: U2.37 (ϕ0); also elsewhere on the board
D0: U2.33 (D0); also elsewhere on the board
D1: U2.32 (D1); also elsewhere on the board
D2: U2.31 (D2); also elsewhere on the board
D3: U2.30 (D3); also elsewhere on the board
D4: U2.29 (D4); also elsewhere on the board
D5: U2.28 (D5); also elsewhere on the board
D6: U2.27 (D6); also elsewhere on the board
D7: U2.26 (D7); also elsewhere on the board
GND: C4.2, U2.21 (VSS); also elsewhere on the board
unnamed: R8.2, U2.2 (RDY)
unnamed: TP4.1, U2.7 (SYNC)
unnamed: TP6.1, U2.5 (~ML)
unnamed: TP5.1, U2.1 (~VP)
R/~W: U2.34 (R/~W); also elsewhere on the board
~CPU2_IRQ: R6.2, U2.4 (~IRQ); also elsewhere on the board
~CPU2_NMI: R7.2, U2.6 (~NMI); also elsewhere on the board
~RESET: U2.40 (~RES); also elsewhere on the board
